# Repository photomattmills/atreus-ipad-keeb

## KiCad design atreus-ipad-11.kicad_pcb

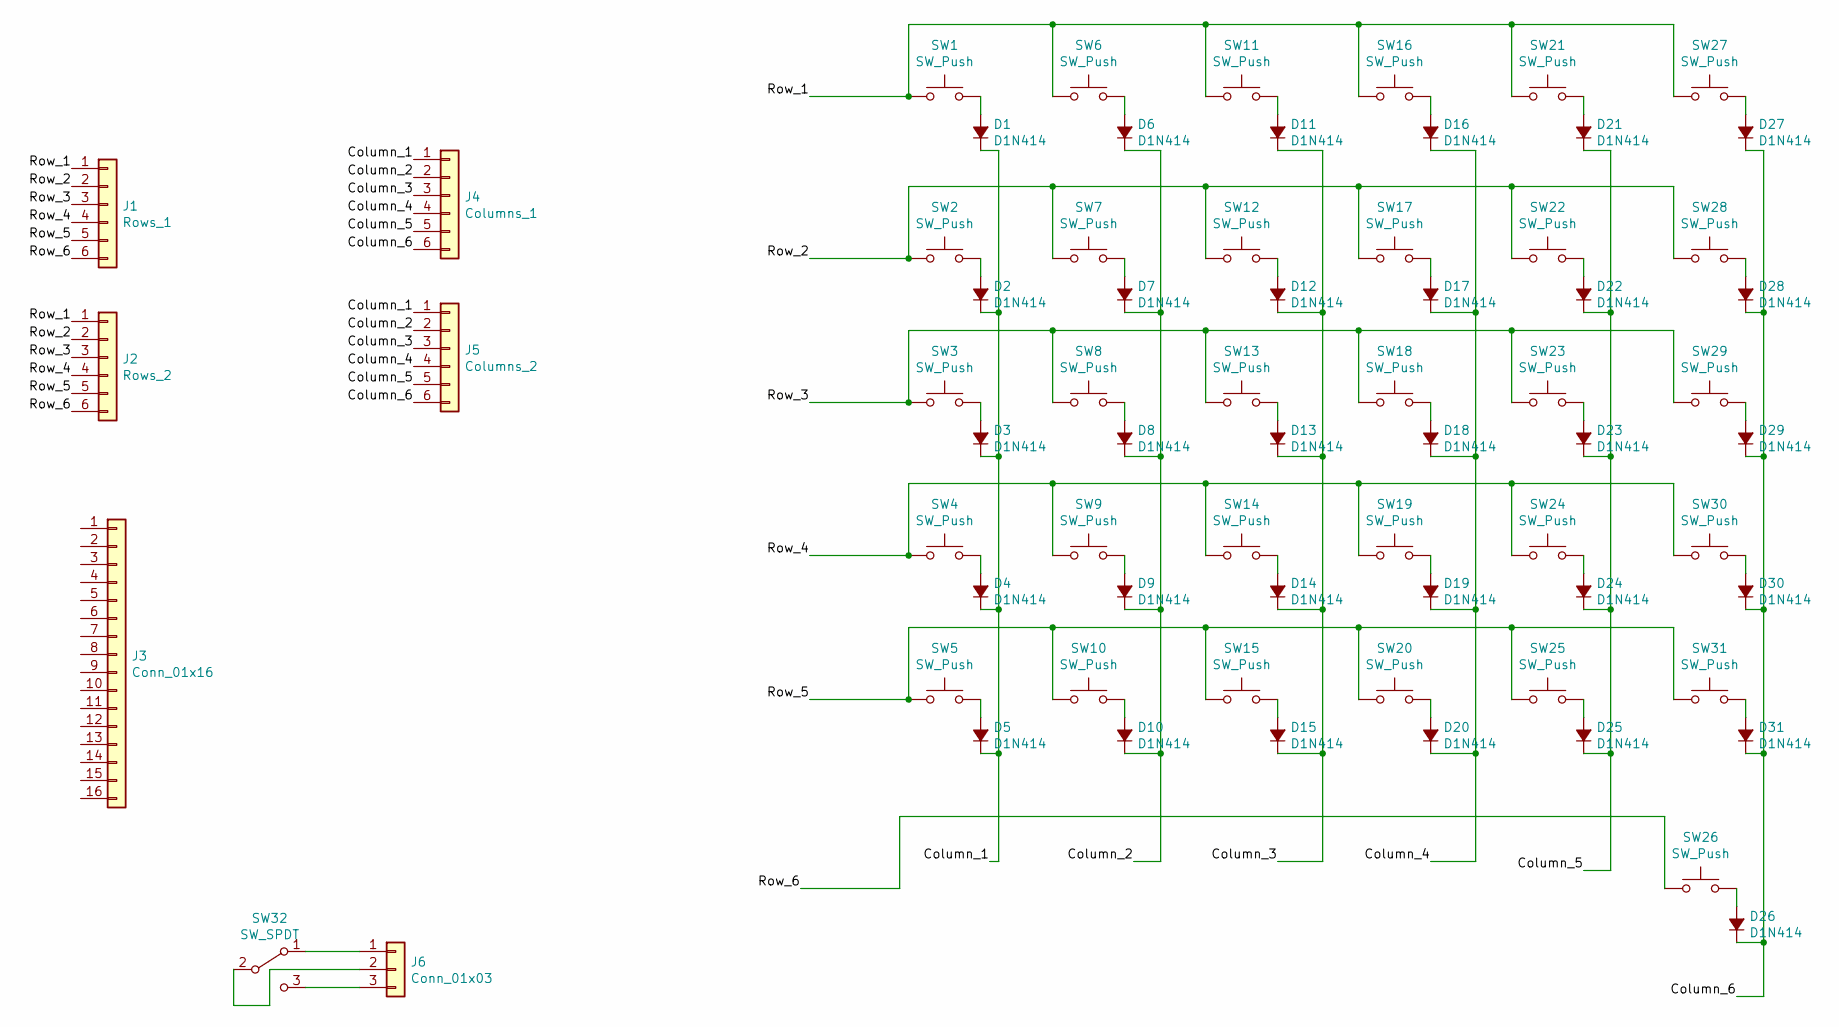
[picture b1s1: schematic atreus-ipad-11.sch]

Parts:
D1, D2, D3, D4, D5, D6, D7, D8, D9, D10, D11, D12, D13, D14, D15, D16, D17, D18, D19, D20, D21, D22, D23, D24, D25, D26, D27, D28, D29, D30, D31: D1N414; D_SOD-123
J1: Rows_1; PinHeader_1x06_P2.00mm_Vertical
J2: Rows_2; PinHeader_1x06_P2.00mm_Vertical
J3: Conn_01x16; PinHeader_1x16_P2.54mm_Vertical
J4: Columns_1; PinHeader_1x06_P2.00mm_Vertical
J5: Columns_2; PinHeader_1x06_P2.00mm_Vertical
J6: Conn_01x03; PinHeader_1x03_P1.27mm_Vertical
SW1, SW2, SW3, SW4, SW5, SW6, SW7, SW8, SW9, SW10, SW11, SW12, SW13, SW14, SW15, SW16, SW17, SW18, SW19, SW20, SW21, SW22, SW23, SW24, SW25, SW26, SW27, SW28, SW29, SW30, SW31: SW_Push; Kailh_low_profile
SW32: SW_SPDT; EQZ1K2-switch

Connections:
/Column_1: D1.1 (K), D2.1 (K), D3.1 (K), D4.1 (K), D5.1 (K), J4.1, J5.1
/Column_2: D6.1 (K), D7.1 (K), D8.1 (K), D9.1 (K), D10.1 (K), J4.2, J5.2
/Column_3: D11.1 (K), D12.1 (K), D13.1 (K), D14.1 (K), D15.1 (K), J4.3, J5.3
/Column_4: D16.1 (K), D17.1 (K), D18.1 (K), D19.1 (K), D20.1 (K), J4.4, J5.4
/Column_5: D21.1 (K), D22.1 (K), D23.1 (K), D24.1 (K), D25.1 (K), J4.5, J5.5
/Column_6: D26.1 (K), D27.1 (K), D28.1 (K), D29.1 (K), D30.1 (K), D31.1 (K), J4.6, J5.6
/Row_1: J1.1, J2.1, SW1.1, SW6.1, SW11.1, SW16.1, SW21.1, SW27.1
/Row_2: J1.2, J2.2, SW2.1, SW7.1, SW12.1, SW17.1, SW22.1, SW28.1
/Row_3: J1.3, J2.3, SW3.1, SW8.1, SW13.1, SW18.1, SW23.1, SW29.1
/Row_4: J1.4, J2.4, SW4.1, SW9.1, SW14.1, SW19.1, SW24.1, SW30.1
/Row_5: J1.5, J2.5, SW5.1, SW10.1, SW15.1, SW20.1, SW25.1, SW31.1
/Row_6: J1.6, J2.6, SW26.1
unnamed: D1.2 (A), SW1.2
unnamed: D2.2 (A), SW2.2
unnamed: D3.2 (A), SW3.2
unnamed: D4.2 (A), SW4.2
unnamed: D5.2 (A), SW5.2
unnamed: D6.2 (A), SW6.2
unnamed: D7.2 (A), SW7.2
unnamed: D8.2 (A), SW8.2
unnamed: D9.2 (A), SW9.2
unnamed: D10.2 (A), SW10.2
unnamed: D11.2 (A), SW11.2
unnamed: D12.2 (A), SW12.2
unnamed: D13.2 (A), SW13.2
unnamed: D14.2 (A), SW14.2
unnamed: D15.2 (A), SW15.2
unnamed: D16.2 (A), SW16.2
unnamed: D17.2 (A), SW17.2
unnamed: D18.2 (A), SW18.2
unnamed: D19.2 (A), SW19.2
unnamed: D20.2 (A), SW20.2
unnamed: D21.2 (A), SW21.2
unnamed: D22.2 (A), SW22.2
unnamed: D23.2 (A), SW23.2
unnamed: D24.2 (A), SW24.2
unnamed: D25.2 (A), SW25.2
unnamed: D26.2 (A), SW26.2
unnamed: D27.2 (A), SW27.2
unnamed: D28.2 (A), SW28.2
unnamed: D29.2 (A), SW29.2
unnamed: D30.2 (A), SW30.2
unnamed: D31.2 (A), SW31.2
unnamed: J6.1, SW32.1 (A)
unnamed: J6.2, SW32.2 (B)
unnamed: J6.3, SW32.3 (C)

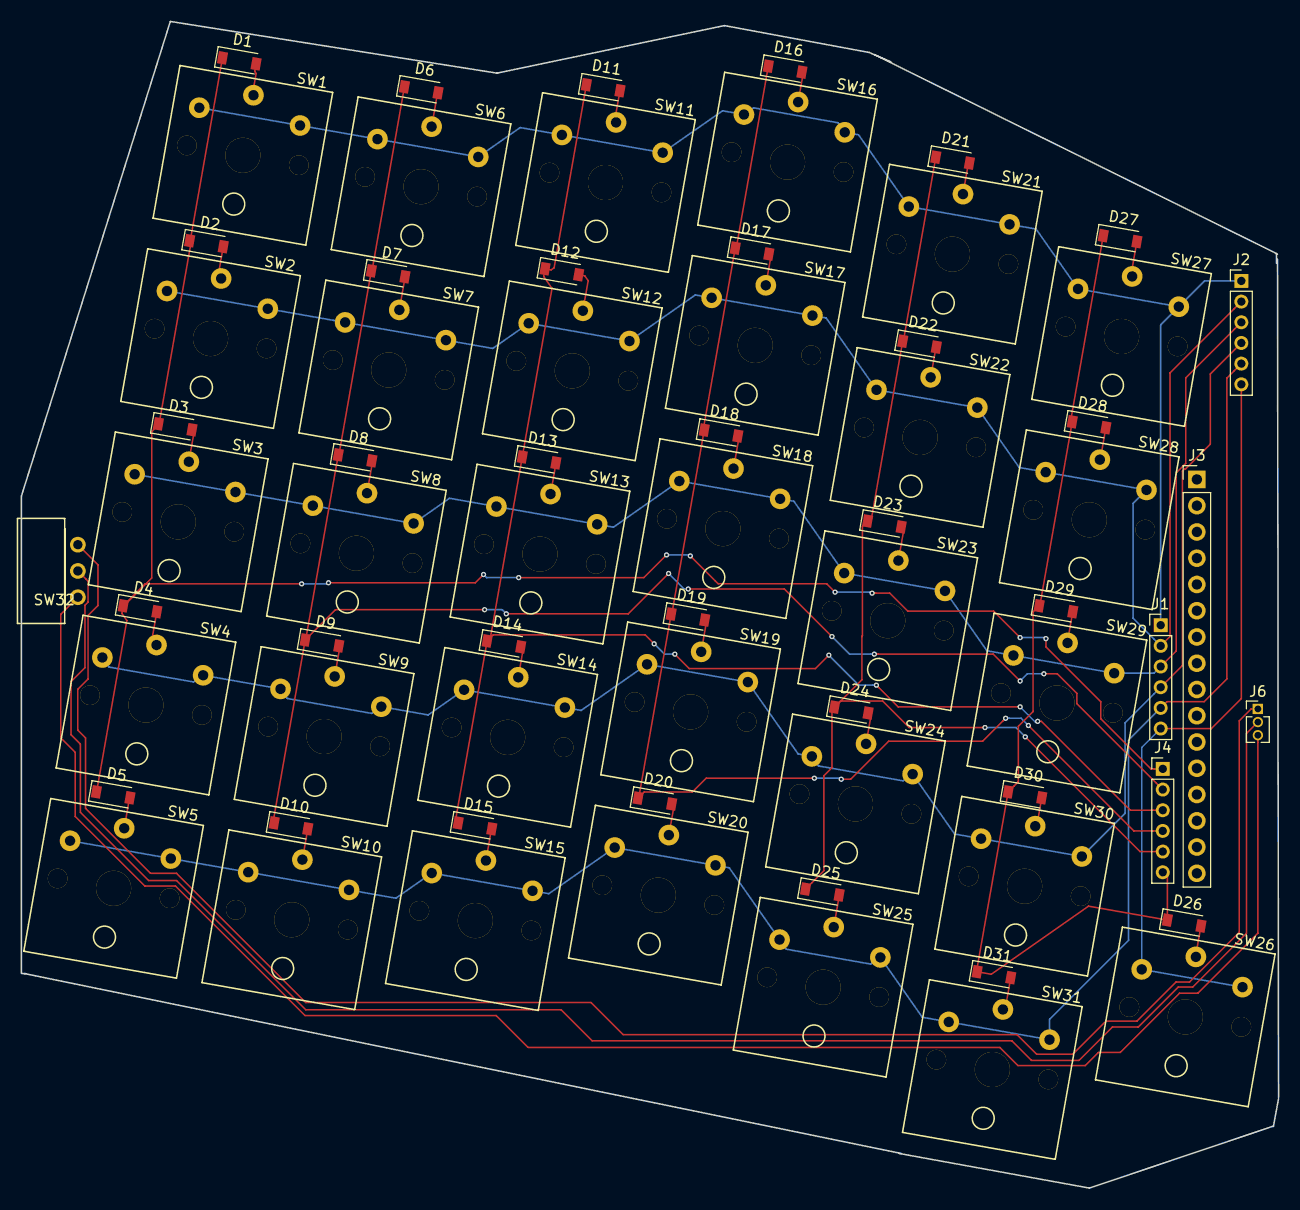
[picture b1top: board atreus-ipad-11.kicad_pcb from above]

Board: 2 copper layers, 121.6 x 112.8 mm, 68 parts (0 on the bottom side), 46 nets.
